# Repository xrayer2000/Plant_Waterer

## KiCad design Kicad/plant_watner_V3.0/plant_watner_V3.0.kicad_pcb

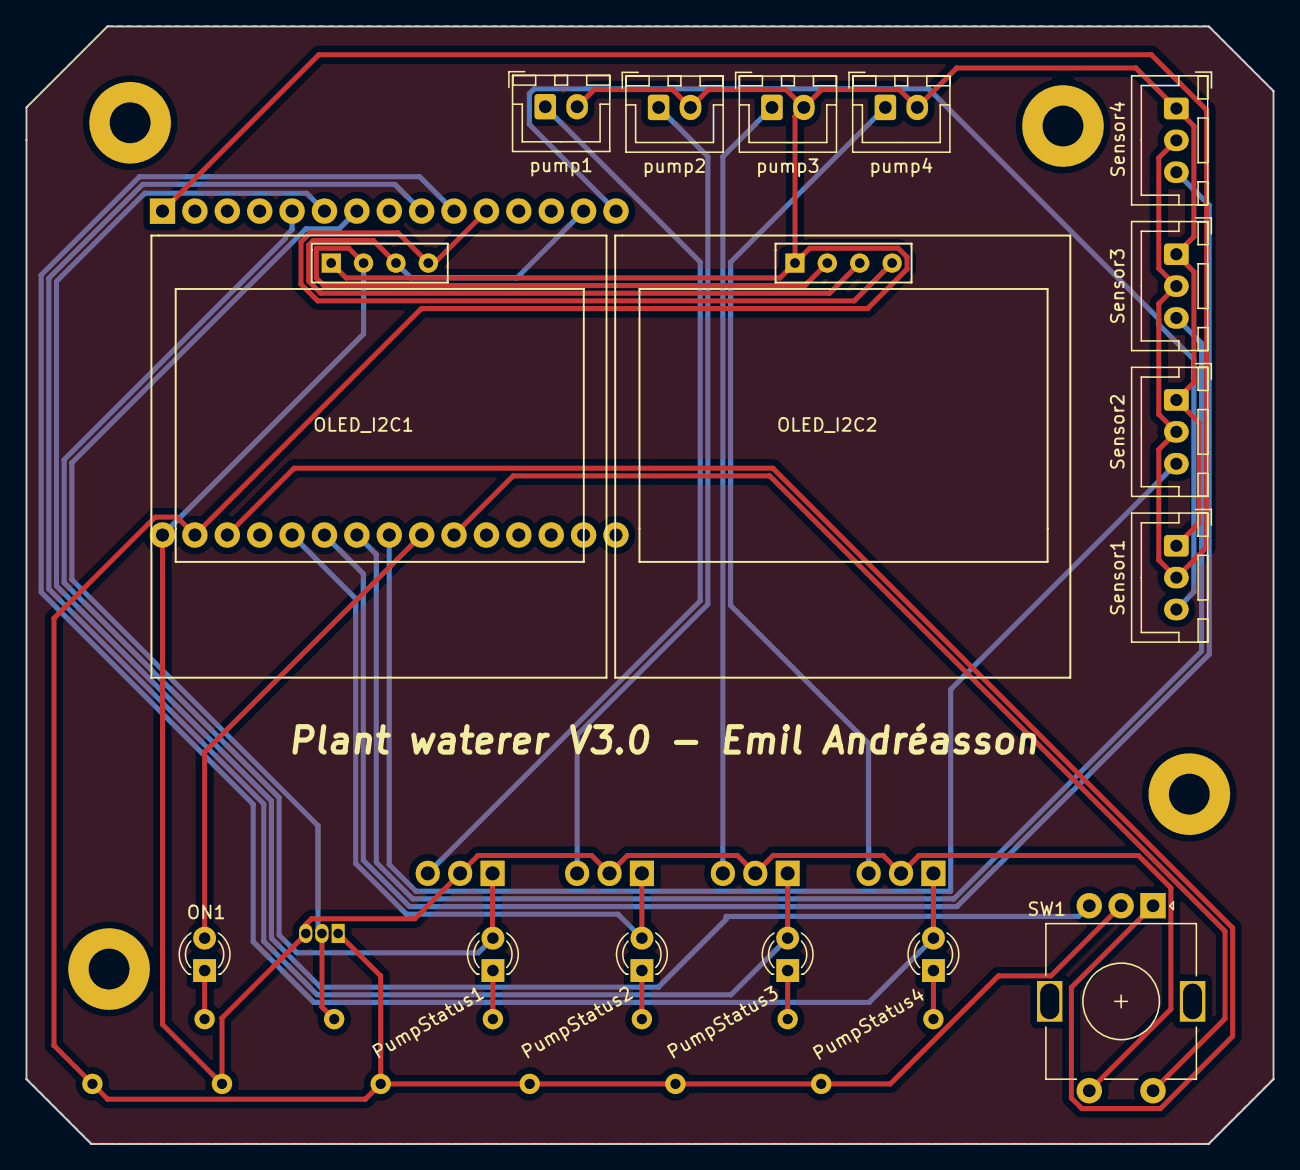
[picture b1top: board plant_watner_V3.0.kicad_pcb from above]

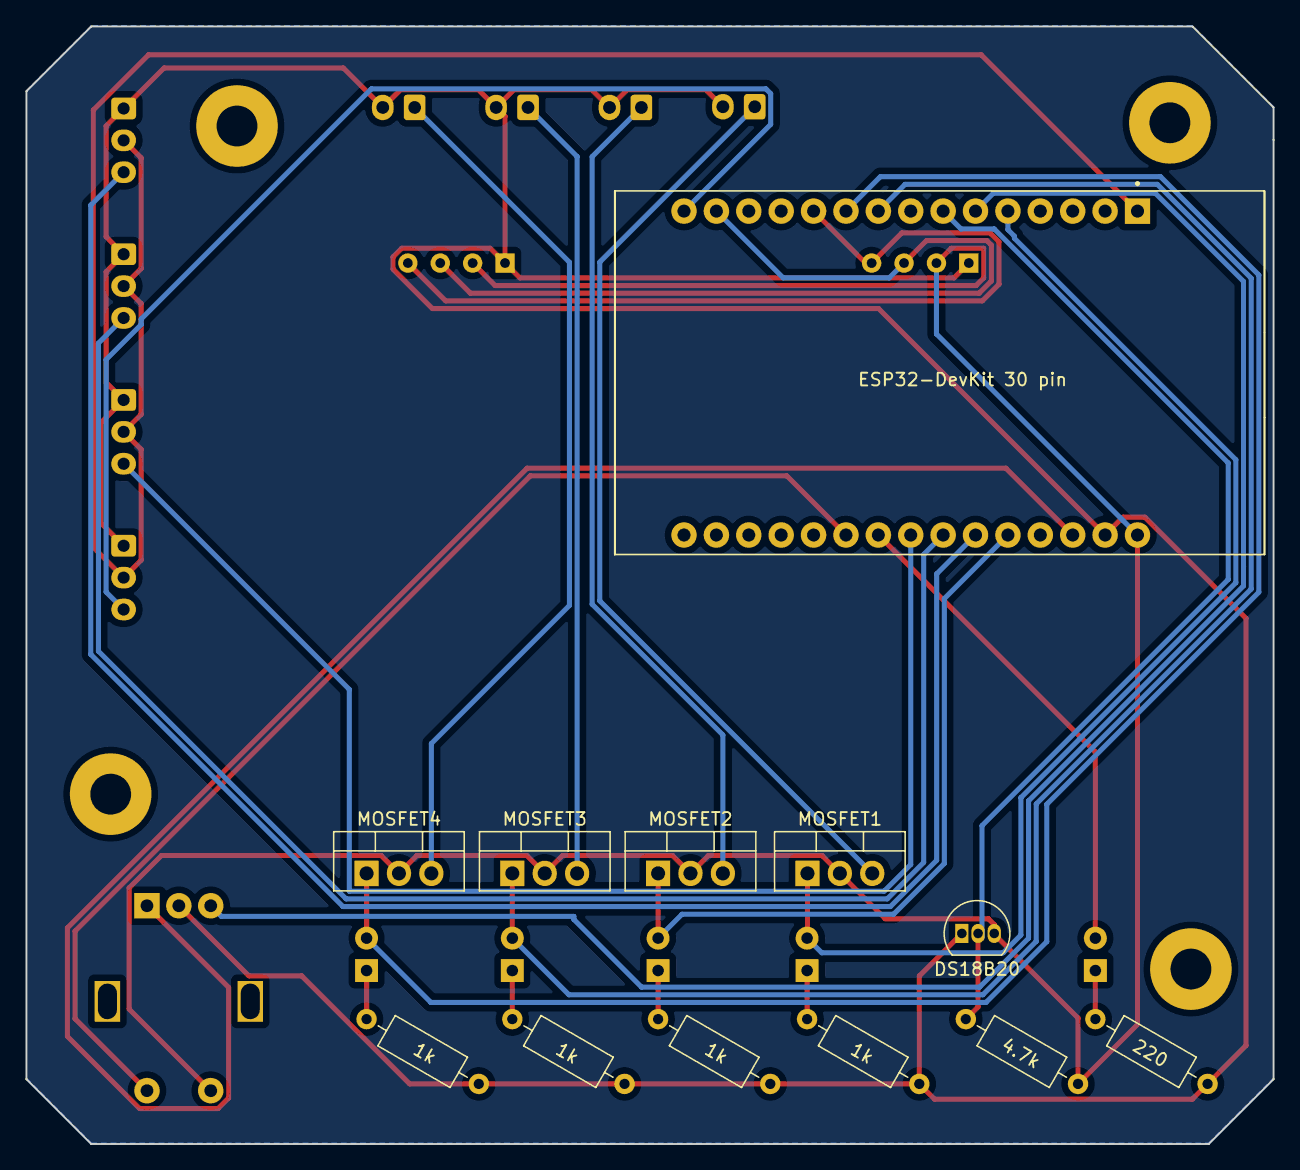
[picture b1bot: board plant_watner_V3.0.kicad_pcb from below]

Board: 2 copper layers, 97.8 x 87.6 mm, 32 parts (12 on the bottom side), 27 nets.

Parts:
ESP32-DevKit 30 pin: ESP32-DEVKIT-V1; MODULE_ESP32_DEVKIT_V1
H1, H2, H3, H4: MountingHole; MountingHole_3.2mm_M3_Pad
J1: Sensor1; JST_XH_B3B-XH-A_1x03_P2.50mm_Vertical
J2: Sensor2; JST_XH_B3B-XH-A_1x03_P2.50mm_Vertical
J3: Sensor3; JST_XH_B3B-XH-A_1x03_P2.50mm_Vertical
J4: Sensor4; JST_XH_B3B-XH-A_1x03_P2.50mm_Vertical
J5: pump1; JST_XH_B2B-XH-A_1x02_P2.50mm_Vertical
J6: pump2; JST_XH_B2B-XH-A_1x02_P2.50mm_Vertical
J7: pump3; JST_XH_B2B-XH-A_1x02_P2.50mm_Vertical
J8: pump4; JST_XH_B2B-XH-A_1x02_P2.50mm_Vertical
MOSFET1, MOSFET2, MOSFET3, MOSFET4: IRLZ44N; TO-220-3_Vertical
OLED_I2C1, OLED_I2C2: SSD1306; ssd1306_1.3''
ON1: LED; LED_D3.0mm
PumpStatus1, PumpStatus2, PumpStatus3, PumpStatus4: LED; LED_D3.0mm
R1: 4.7k; R_Axial_DIN0207_L6.3mm_D2.5mm_P10.16mm_Horizontal
R2: 220; R_Axial_DIN0207_L6.3mm_D2.5mm_P10.16mm_Horizontal
R3, R4, R5, R6: 1k; R_Axial_DIN0207_L6.3mm_D2.5mm_P10.16mm_Horizontal
SW1: Rotary_Encoder_Switch; RotaryEncoder_Alps_EC11E-Switch_Vertical_H20mm
Temp_sensor1: DS18B20; TO-92L_Inline

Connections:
unnamed: ESP32-DevKit 30 pin.1 (3V3), J1.2, J2.2, J3.2, J4.2
unnamed: ESP32-DevKit 30 pin.5 (D4), MOSFET1.1 (G), PumpStatus1.2 (A)
unnamed: ESP32-DevKit 30 pin.28 (D13), SW1.A
unnamed: ESP32-DevKit 30 pin.26 (D14), MOSFET2.1 (G), PumpStatus2.2 (A)
unnamed: ESP32-DevKit 30 pin.9 (D18), MOSFET3.1 (G), PumpStatus3.2 (A)
unnamed: ESP32-DevKit 30 pin.10 (D19), MOSFET4.1 (G), PumpStatus4.2 (A)
unnamed: ESP32-DevKit 30 pin.11 (D21), OLED_I2C1.4 (SDA), OLED_I2C2.4 (SDA)
unnamed: ESP32-DevKit 30 pin.14 (D22), OLED_I2C1.3 (SCL), OLED_I2C2.3 (SCL)
unnamed: ESP32-DevKit 30 pin.15 (D23), J1.3
unnamed: ESP32-DevKit 30 pin.23 (D25), J2.3
unnamed: ESP32-DevKit 30 pin.24 (D26), J3.3
unnamed: ESP32-DevKit 30 pin.25 (D27), J4.3
unnamed: ESP32-DevKit 30 pin.21 (D32), SW1.S2
unnamed: ESP32-DevKit 30 pin.22 (D33), ON1.2 (A)
unnamed: ESP32-DevKit 30 pin.6 (RX2), SW1.B
unnamed: ESP32-DevKit 30 pin.7 (TX2), R1.1, Temp_sensor1.2 (DQ)
unnamed: ESP32-DevKit 30 pin.30 (VIN), MOSFET1.2 (D), MOSFET2.2 (D), MOSFET3.2 (D), MOSFET4.2 (D), OLED_I2C1.2 (VCC), OLED_I2C2.2 (VCC), R1.2, SW1.S1, Temp_sensor1.3 (VDD)
unnamed: ESP32-DevKit 30 pin.29 (GND), J1.1, J2.1, J3.1, J4.1, J5.2, J6.2, J7.2, J8.2, OLED_I2C1.1 (GND), OLED_I2C2.1 (GND), R2.2, R3.2, R4.2, R5.2, R6.2, SW1.C, Temp_sensor1.1 (GND)
unnamed: J5.1, MOSFET1.3 (S)
unnamed: J6.1, MOSFET2.3 (S)
unnamed: J7.1, MOSFET3.3 (S)
unnamed: J8.1, MOSFET4.3 (S)
unnamed: ON1.1 (K), R2.1
unnamed: PumpStatus1.1 (K), R3.1
unnamed: PumpStatus2.1 (K), R4.1
unnamed: PumpStatus3.1 (K), R5.1
unnamed: PumpStatus4.1 (K), R6.1

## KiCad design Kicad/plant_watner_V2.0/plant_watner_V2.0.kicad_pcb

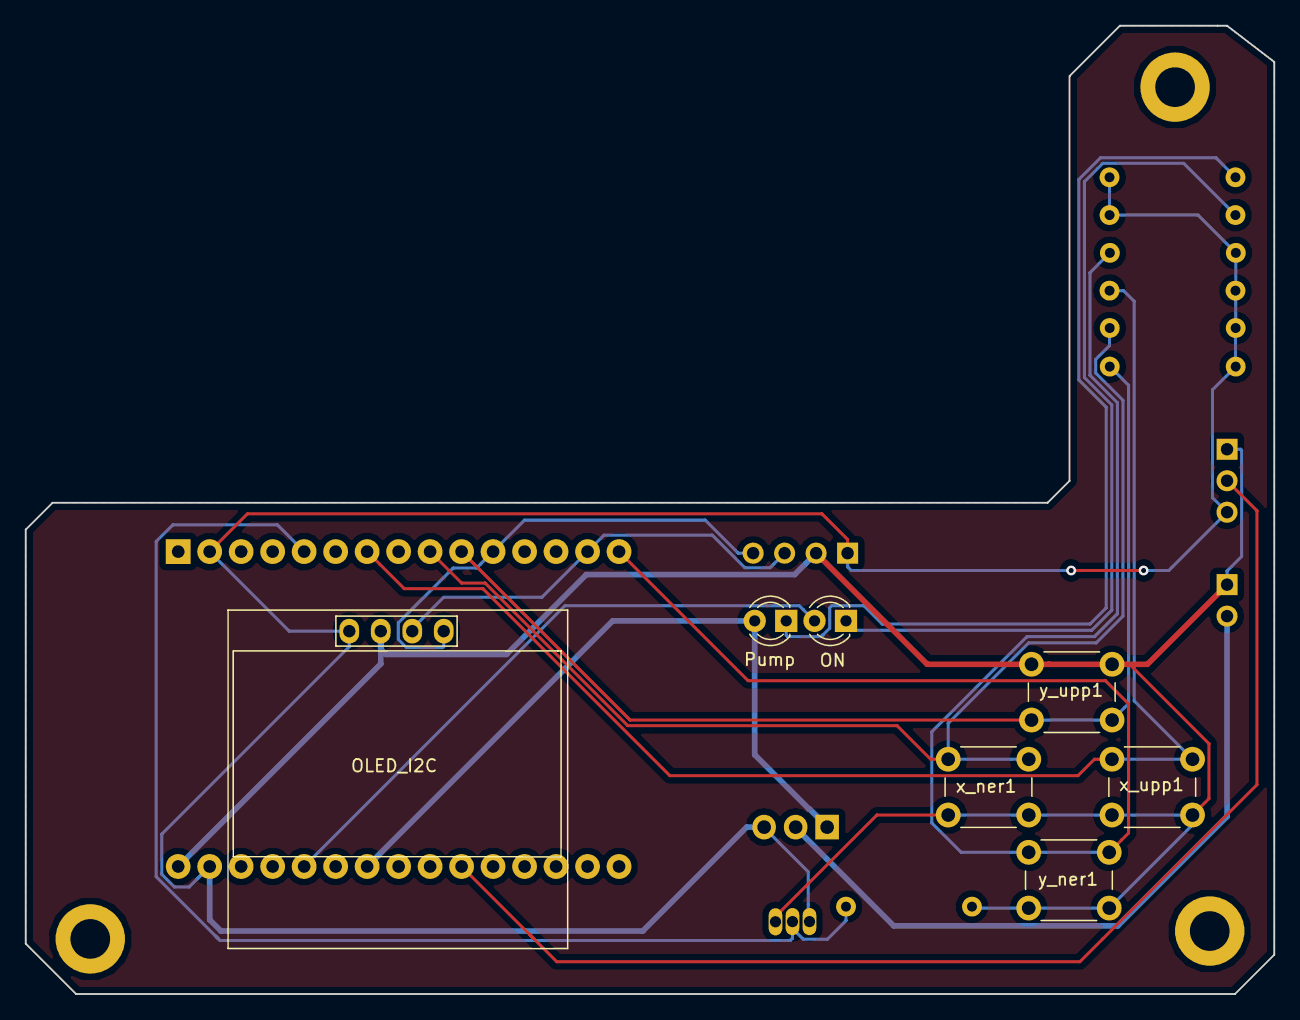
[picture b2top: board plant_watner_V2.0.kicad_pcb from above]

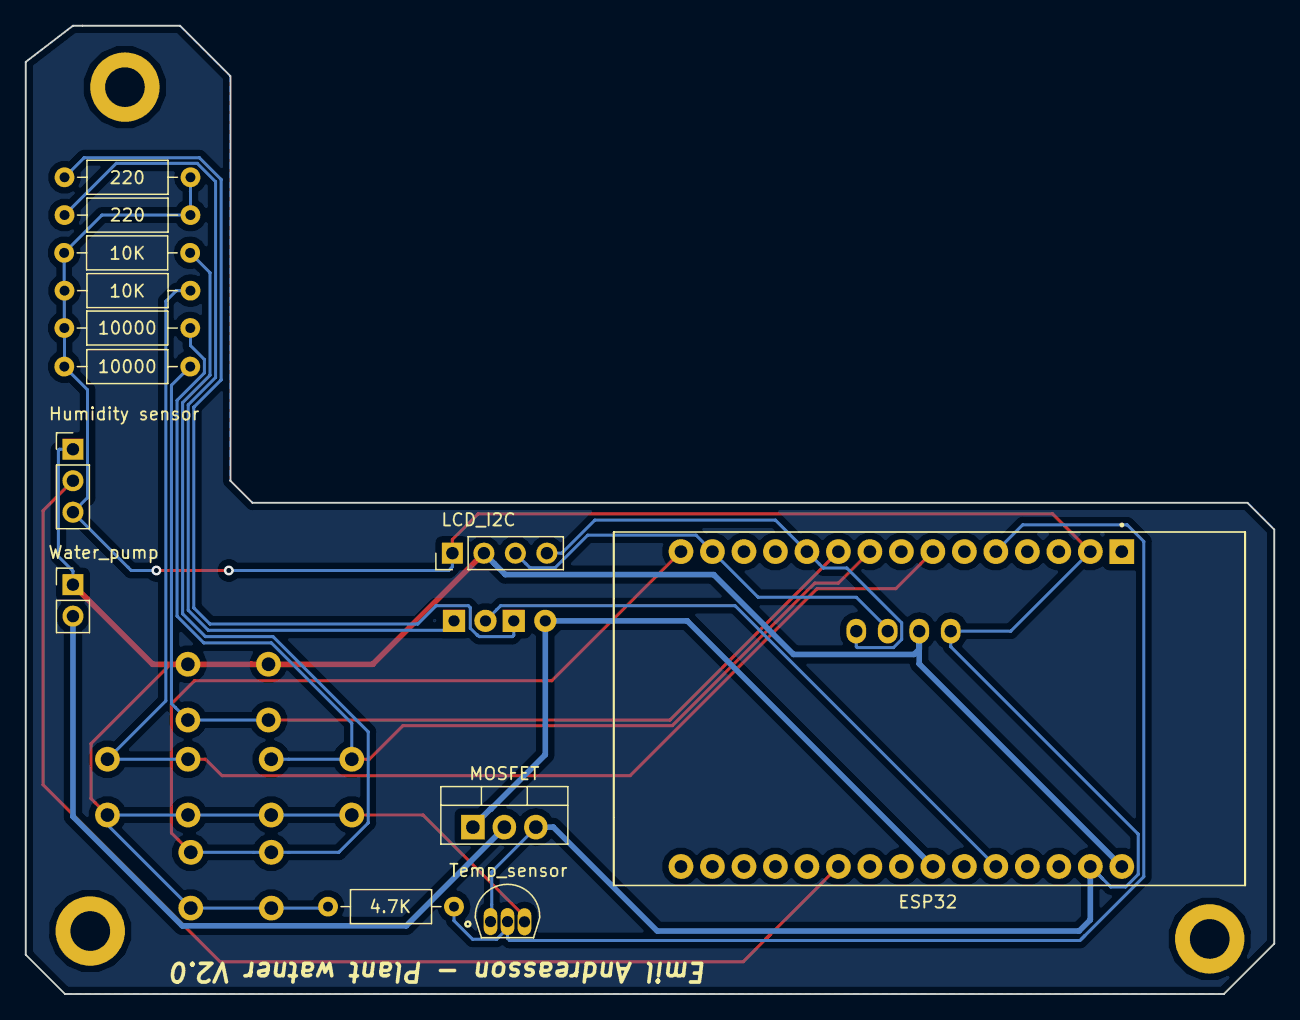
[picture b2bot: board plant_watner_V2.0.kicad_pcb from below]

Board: 2 copper layers, 100.7 x 78.1 mm, 20 parts (13 on the bottom side), 15 nets.

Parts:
4.7K: R; R_Axial_DIN0207_L6.3mm_D2.5mm_P10.16mm_Horizontal
10K, 10K#2, 10000, 10000#2: 10000; R_Axial_DIN0207_L6.3mm_D2.5mm_P10.16mm_Horizontal
220, 220#2: 220; R_Axial_DIN0207_L6.3mm_D2.5mm_P10.16mm_Horizontal
ESP32: ESP32-DEVKIT-V1; MODULE_ESP32_DEVKIT_V1
Humidity sensor: HumiditySensor; PinHeader_1x03_P2.54mm_Vertical
LCD_I2C: hd44780; PinHeader_1x04_P2.54mm_Vertical
MOSFET: IRLZ44N; TO-220-3_Vertical
OLED_I2C: SSD1306; 128x64OLED
ON: LED; LED_D3.0mm
Pump: LED; LED_D3.0mm
Temp_sensor: DS18B20; XDCR_TMP36GT9
Water_pump: Motor_DC; PinHeader_1x02_P2.54mm_Vertical
x_ner1: SW_Push; SW_PUSH_6mm
x_upp1: SW_Push; SW_PUSH_6mm
y_ner1: SW_Push; SW_PUSH_6mm
y_upp1: SW_Push; SW_PUSH_6mm

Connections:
unnamed: 10K.1, 10K#2.1, 220.2, 220#2.2, 10000.1, 10000#2.1, ESP32.2, ESP32.29, Humidity sensor.3, LCD_I2C.1, MOSFET.3, OLED_I2C.1, Temp_sensor.1
unnamed: 4.7K.2, ESP32.5, Temp_sensor.2
unnamed: 10K.2, ESP32.7, x_upp1.1
unnamed: 10000#2.2, ESP32.9, x_ner1.1
unnamed: 10000.2, ESP32.10, y_upp1.1
unnamed: ESP32.11, LCD_I2C.4, OLED_I2C.4
unnamed: ESP32.14, LCD_I2C.3, OLED_I2C.3
unnamed: 10K#2.2, ESP32.15, y_ner1.1
unnamed: ESP32.21, Humidity sensor.2
unnamed: ESP32.24, MOSFET.1, Pump.2
unnamed: ESP32.26, ON.2
unnamed: 4.7K.1, ESP32.30, Humidity sensor.1, LCD_I2C.2, OLED_I2C.2, Temp_sensor.3, Water_pump.1, x_ner1.2, x_upp1.2, y_ner1.2, y_upp1.2
unnamed: MOSFET.2, Water_pump.2
unnamed: 220.1, ON.1
unnamed: 220#2.1, Pump.1

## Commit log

2025-06-16 added plant waterer V3.0 Kicad, and moddified the arduino code
2025-07-17 version 3.0 plant waterer
